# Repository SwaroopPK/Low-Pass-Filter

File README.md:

# Sallen Key Low-Pass-Filter

 This is a simple Sallen key circuit designed using KiCad. A SallenKey Low Pass Filter is a circuit which allows low frequency
 signals to pass through and blocks the higher frequency signal. The enclosed circuit is designed to obtain a cut-off frequency of 100KHz and the components aree chosen in order to obtain the required cut-off.
 
## Components Included:-

  * OpAmp:- AD8051
       ( *AD8051 datasheet for reference* [Datasheet_AD8051](https://www.analog.com/media/en/technical-documentation/data-sheets/AD8051_8052_8054.pdf) )
 
  * Resistors:- 2k and 110 ohm
  
  * Capacitors:- 2.2nF and 5.1nF
 
  * Battery:- 3V ×2 
 
   A library for AD8051 was manually created in KiCad.
 Also a footprint for AD8051(8 lead MSOP module) was created according to the datasheet.
 A PCB design was made and connections were made.

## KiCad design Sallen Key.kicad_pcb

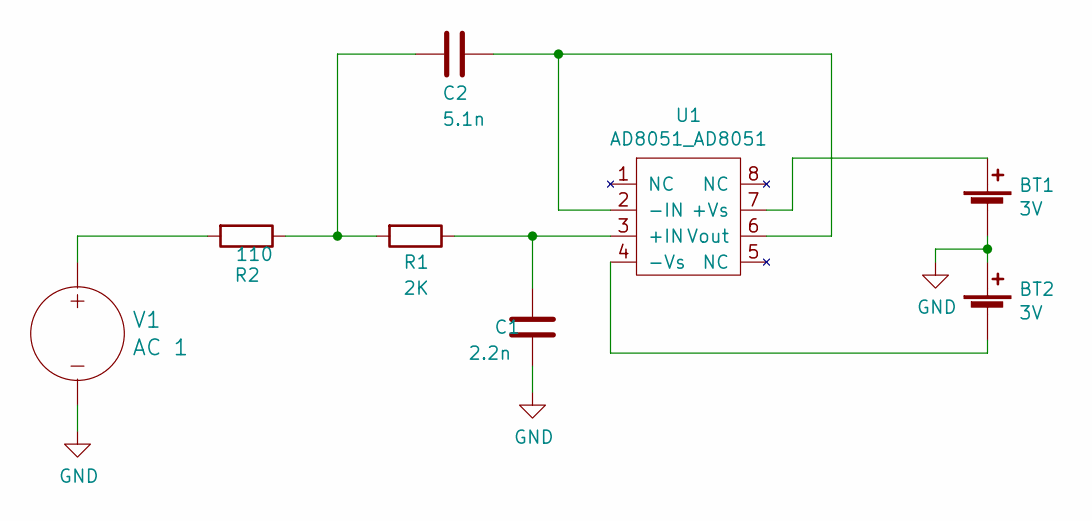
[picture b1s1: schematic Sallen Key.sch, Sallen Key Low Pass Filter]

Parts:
BT1, BT2: 3V; BatteryHolder_Keystone_107_1x23mm
C1: 2.2n; C_Rect_L7.2mm_W2.5mm_P5.00mm_FKS2_FKP2_MKS2_MKP2
C2: 5.1n; C_Rect_L18.0mm_W6.0mm_P15.00mm_FKS3_FKP3
R1: 2K; R_Axial_DIN0207_L6.3mm_D2.5mm_P10.16mm_Horizontal
R2: 110; R_Axial_DIN0207_L6.3mm_D2.5mm_P10.16mm_Horizontal
U1: AD8051_AD8051; AD8051-SOIC-8
V1: AC 1; TerminalBlock_4Ucon_1x02_P3.50mm_Horizontal

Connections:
GND: BT1.2 (-), BT2.1 (+), C1.2, V1.2 (-)
unnamed: BT1.1 (+), U1.7 (+Vs)
unnamed: BT2.2 (-), U1.4 (-Vs)
unnamed: C1.1, R1.1, U1.3 (+IN)
unnamed: C2.1, U1.2 (-IN), U1.6 (Vout)
unnamed: C2.2, R1.2, R2.1
unnamed: R2.2, V1.1 (+)

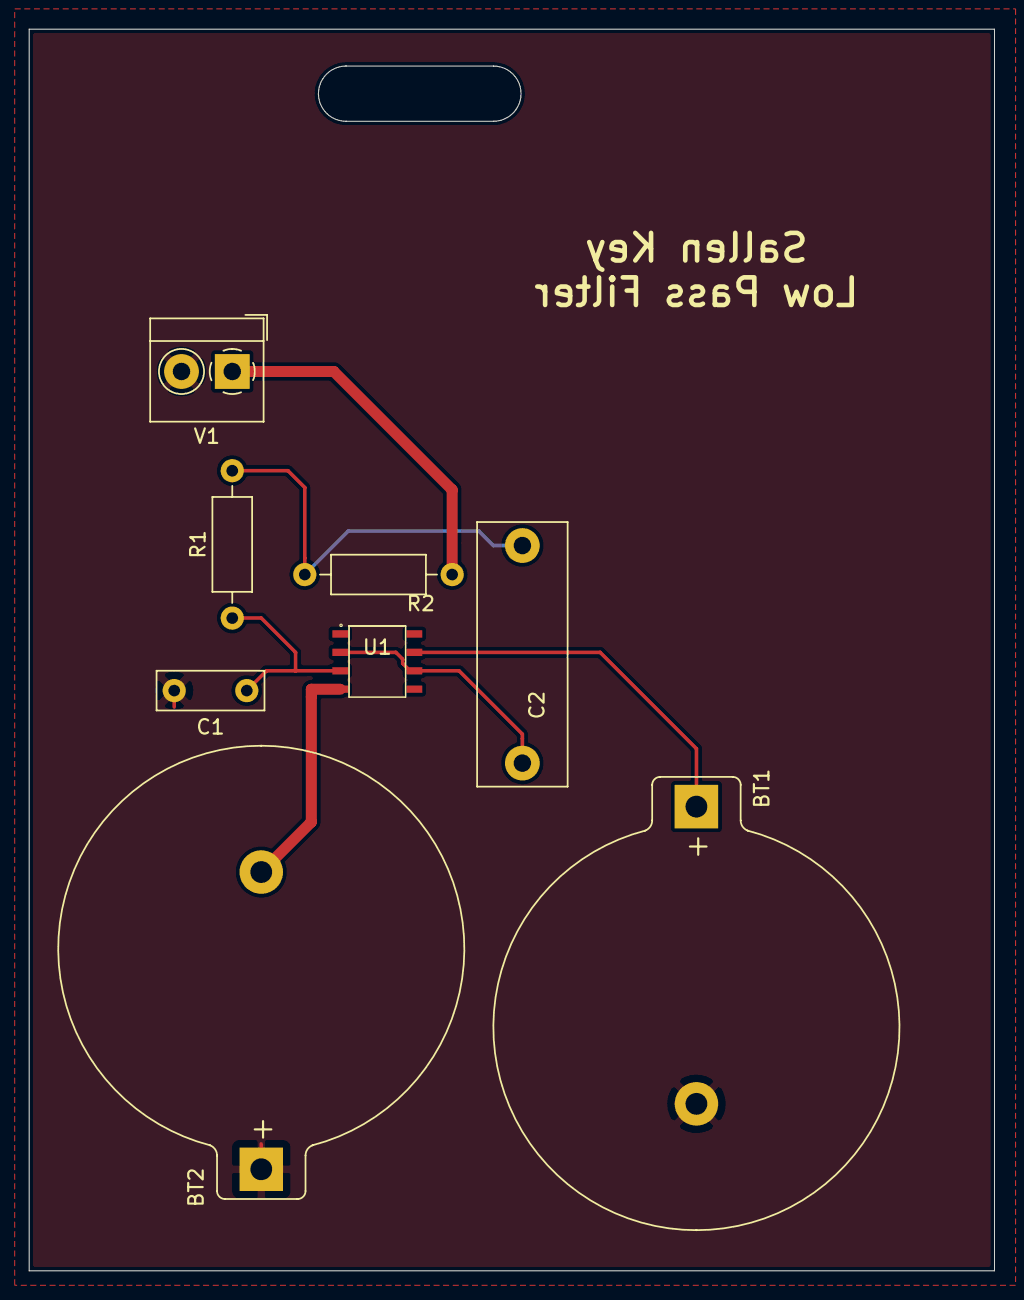
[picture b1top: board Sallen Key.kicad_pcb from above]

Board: 2 copper layers, 66.5 x 85.6 mm, 8 parts (0 on the bottom side), 7 nets.

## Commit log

2019-06-09 Update README.md
    Added AD8051 datasheet
